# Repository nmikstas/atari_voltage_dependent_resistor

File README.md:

# atari_voltage_dependent_resistor
The source files for the reproduction of Atari voltage dependent resistor PCB. The PCB is designed with Kicad. Completed and verified working.

# Folder Structure
* BOM - Bill of materials for the Atari varistor replacement PCB
* gerbers -The gerber files for the Atari varistor replacement PCB
* pcb - The Kicad design files for the Atari varistor replacement PCB

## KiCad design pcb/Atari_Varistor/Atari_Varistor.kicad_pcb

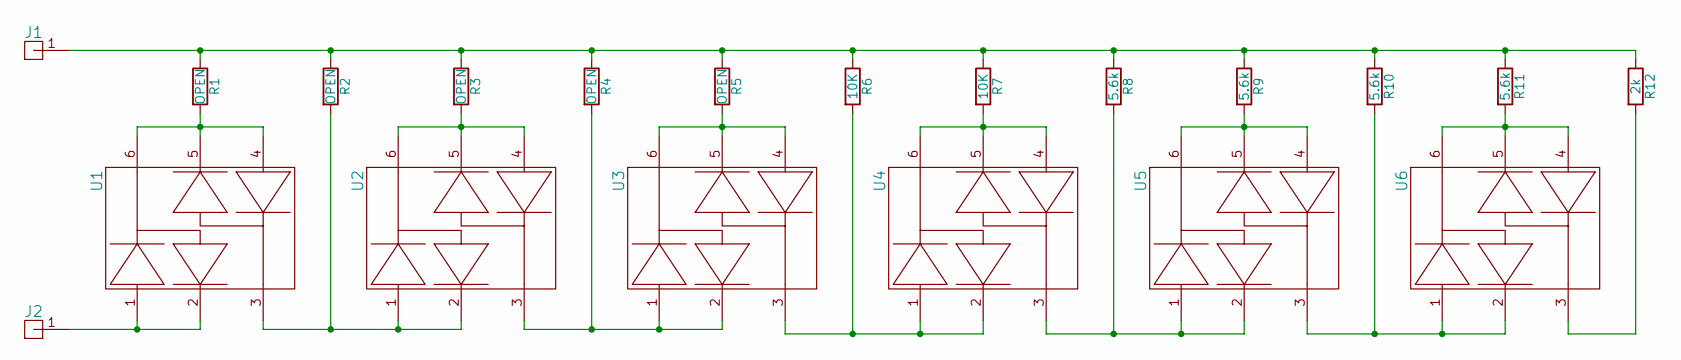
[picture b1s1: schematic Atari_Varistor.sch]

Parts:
J1, J2: CONN PC PIN CIRC 0.020DIA GOLD; Pin; Digikey Part Number ED90539-ND
R1, R2, R3, R4, R5: OPEN; R_0402; Digikey Part Number N/A
R6, R7: 10K; R_0402; Digikey Part Number 311-10.0KLRCT-ND
R8, R9, R10, R11: 5.6k; R_0402; Digikey Part Number 311-5.6KLRCT-ND
R12: 2k; R_0402; Digikey Part Number 311-2KLRCT-ND
U1, U2, U3, U4, U5, U6: DIODE ARRAY GP 75V 215MA SOT363; DiodeArray; Digikey Part Number BAV99DW-FDICT-ND

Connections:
unnamed: J1.1, R1.1, R2.1, R3.1, R4.1, R5.1, R6.1, R7.1, R8.1, R9.1, R10.1, R11.1, R12.1
unnamed: J2.1, U1.1, U1.2
unnamed: R1.2, U1.4, U1.5, U1.6
unnamed: R2.2, U1.3, U2.1, U2.2
unnamed: R3.2, U2.4, U2.5, U2.6
unnamed: R4.2, U2.3, U3.1, U3.2
unnamed: R5.2, U3.4, U3.5, U3.6
unnamed: R6.2, U3.3, U4.1, U4.2
unnamed: R7.2, U4.4, U4.5, U4.6
unnamed: R8.2, U4.3, U5.1, U5.2
unnamed: R9.2, U5.4, U5.5, U5.6
unnamed: R10.2, U5.3, U6.1, U6.2
unnamed: R11.2, U6.4, U6.5, U6.6
unnamed: R12.2, U6.3

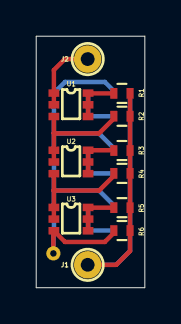
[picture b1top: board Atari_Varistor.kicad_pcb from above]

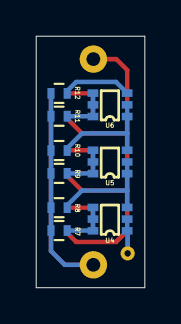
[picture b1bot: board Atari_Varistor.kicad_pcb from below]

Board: 2 copper layers, 6.0 x 14.0 mm, 20 parts (9 on the bottom side), 14 nets.

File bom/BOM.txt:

Reference           Quantity    Value                             Digikey Part Number
J1 J2               2           CONN PC PIN CIRC 0.020DIA GOLD    ED90539-ND
R10 R11 R8 R9       4           5.6k                              311-5.6KLRCT-ND
R12                 1           2k                                311-2KLRCT-ND
R1 R2 R3 R4 R5      5           OPEN                              N/A
R6 R7               2           10K                               311-10.0KLRCT-ND
U1 U2 U3 U4 U5 U6   6           DIODE ARRAY GP 75V 215MA SOT363   BAV99DW-FDICT-ND

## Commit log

2021-05-24 Moved project into git
